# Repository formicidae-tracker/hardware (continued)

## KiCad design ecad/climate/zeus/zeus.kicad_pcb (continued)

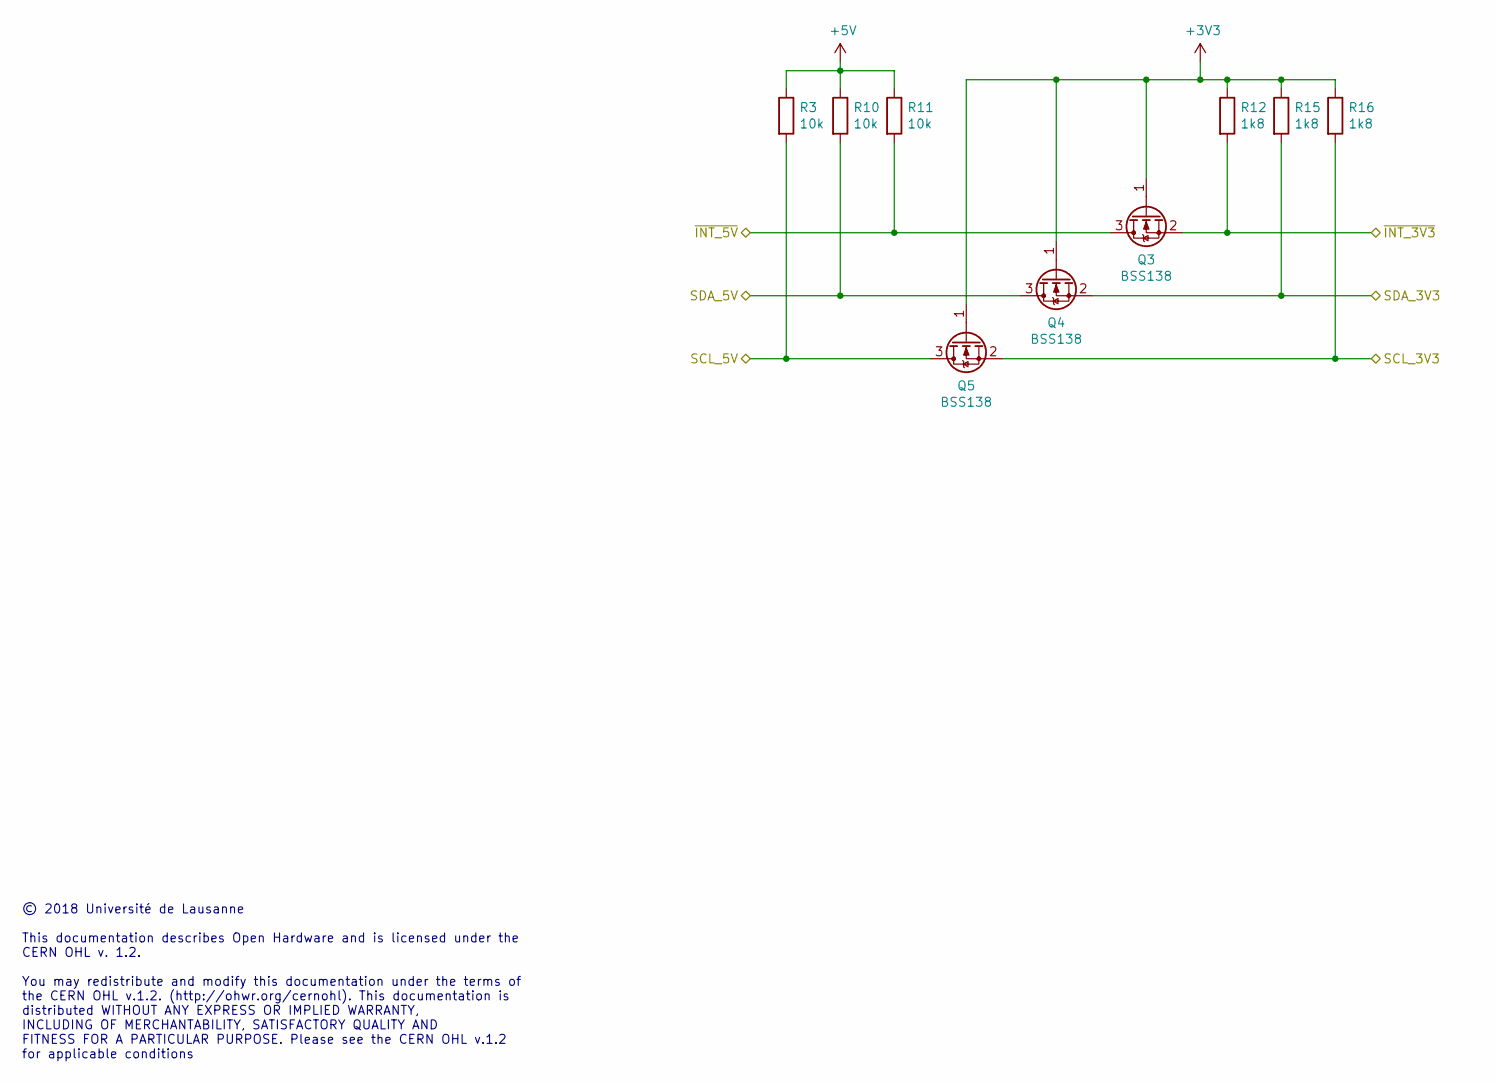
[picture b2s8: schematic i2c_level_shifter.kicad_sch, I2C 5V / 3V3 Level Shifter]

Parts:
Q3, Q4, Q5: BSS138; SOT-23; MPN BSS138
R3, R10, R11: 10k; R_0603_1608Metric; MPN GPR060310K
R12, R15, R16: 1k8; R_0603_1608Metric; MPN GPR06031K8

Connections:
+3V3: Q3.1 (G), Q4.1 (G), Q5.1 (G), R12.1, R15.1, R16.1; also elsewhere on the board
+5V: R3.1, R10.1, R11.1; also elsewhere on the board
/Fan PWM Controller 1/SCL: Q5.2 (S), R16.2; also elsewhere on the board
/Fan PWM Controller 1/SDA: Q4.2 (S), R15.2; also elsewhere on the board
/Fan PWM Controller 1/~ALERT: Q3.2 (S), R12.2; also elsewhere on the board
/I2C Level Shifter/SCL_5V: Q5.3 (D), R3.2; also elsewhere on the board
/I2C Level Shifter/SDA_5V: Q4.3 (D), R10.2; also elsewhere on the board
/I2C Level Shifter/~INT_5V: Q3.3 (D), R11.2; also elsewhere on the board

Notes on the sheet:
© 2018 Université de Lausanne This documentation describes Open Hardware and is licensed under the CERN OHL v. 1.2. You may redistribute and modify this documentation under the terms of the CERN OHL v.1.2. (http://ohwr.org/cernohl). This documentation is distributed WITHOUT ANY EXPRESS OR IMPLIED W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

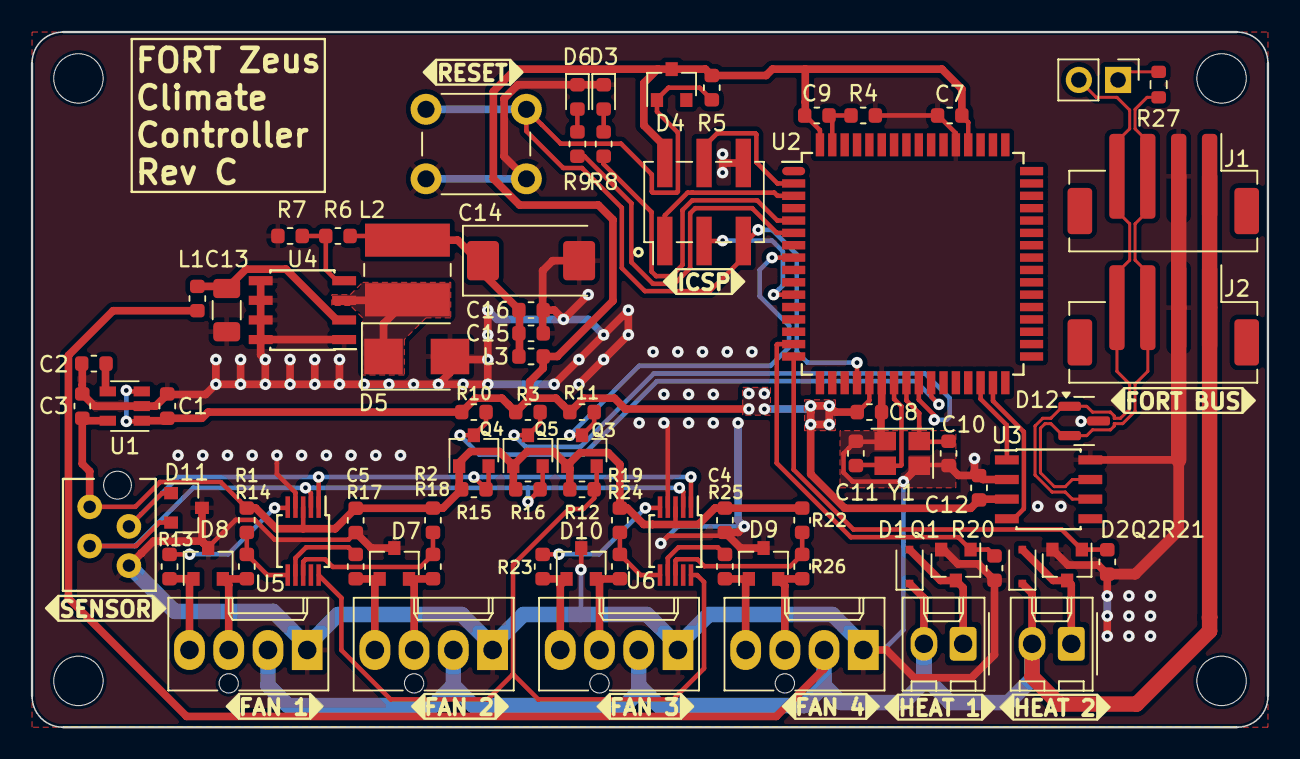
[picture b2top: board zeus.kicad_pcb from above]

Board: 2 copper layers, 80.0 x 45.0 mm, 81 parts (0 on the bottom side), 51 nets.

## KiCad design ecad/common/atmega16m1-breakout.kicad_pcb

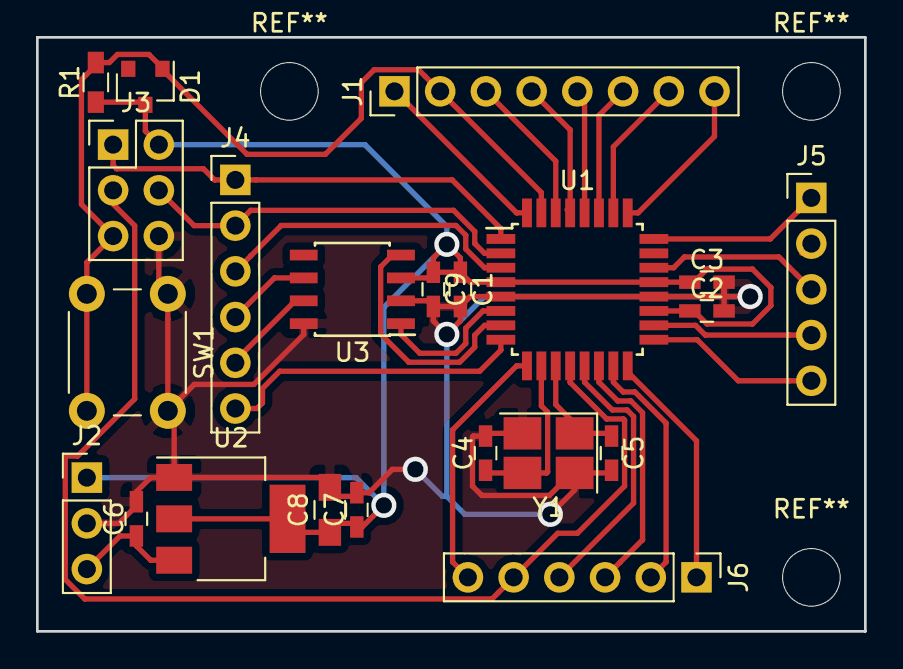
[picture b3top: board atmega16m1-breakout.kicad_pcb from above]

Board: 2 copper layers, 46.0 x 33.0 mm, 22 parts (0 on the bottom side), 32 nets.

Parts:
C1, C2, C3, C6, C7, C9: 100nF; C_0603_HandSoldering
C4, C5: 18pF; C_0603_HandSoldering
C8: 22uF; C_0805_HandSoldering
D1: D_Schottky; D_SOT-23_ANK
J1: Conn_01x08; Pin_Header_Straight_1x08_Pitch2.54mm
J2: Conn_01x03; Pin_Header_Straight_1x03_Pitch2.54mm
J3: Conn_02x03_Odd_Even; Pin_Header_Straight_2x03_Pitch2.54mm
J4, J6: Conn_01x06; Pin_Header_Straight_1x06_Pitch2.54mm
J5: Conn_01x05; Pin_Header_Straight_1x05_Pitch2.54mm
R1: 100K; R_0603_HandSoldering
SW1: SW_Push; SW_PUSH_6mm
U1: ATMEGA16M1-AU; TQFP-32_7x7mm_Pitch0.8mm
U2: NCP1117-5.0_SOT223; SOT-223-3Lead_TabPin2
U3: MCP2561-E/SN; SOIC-8_3.9x4.9mm_Pitch1.27mm
Y1: 16MHz; Crystal_SMD_SeikoEpson_FA238-4pin_3.2x2.5mm_HandSoldering

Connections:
+5V: C1.1, C2.1, C3.1, C7.1, C8.1, C9.1, D1.1, J2.1, J3.2, R1.1, U1.4, U1.19, U1.21, U2.2, U3.3
+BATT: C6.1, J2.3, U2.3
/1: J3.1, J4.1, U1.1
/2: J3.4, J4.2, U1.2
/3: J4.3, U1.3
/8: J4.6, U1.8
/9: J6.6, U1.9
/12: J3.3, J6.5, U1.12
/13: J6.4, U1.13
/14: J6.3, U1.14
/15: J6.2, U1.15
/16: J6.1, U1.16
/17: J5.5, U1.17
/18: J5.4, U1.18
/22: J5.3, U1.22
/23: J5.2, U1.23
/24: J5.1, U1.24
/25: J1.8, U1.25
/26: J1.7, U1.26
/27: J1.6, U1.27
/28: J1.5, U1.28
/29: J1.4, U1.29
/30: J1.3, U1.30
/31: D1.2, J1.2, J3.5, R1.2, SW1.2, U1.31
/32: J1.1, U1.32
/CAN+: J4.5, U3.7
/CAN-: J4.4, U3.6
/RXCAN: U1.7, U3.4
/TXCAN: U1.6, U3.1
/XTAL+: C4.1, U1.10, Y1.3
/XTAL-: C5.1, U1.11, Y1.1
GND: C1.2, C2.2, C3.2, C4.2, C5.2, C6.2, C7.2, C8.2, C9.2, J2.2, J3.6, SW1.1, U1.5, U1.20, U2.1, U3.2, U3.8, Y1.2, Y1.4

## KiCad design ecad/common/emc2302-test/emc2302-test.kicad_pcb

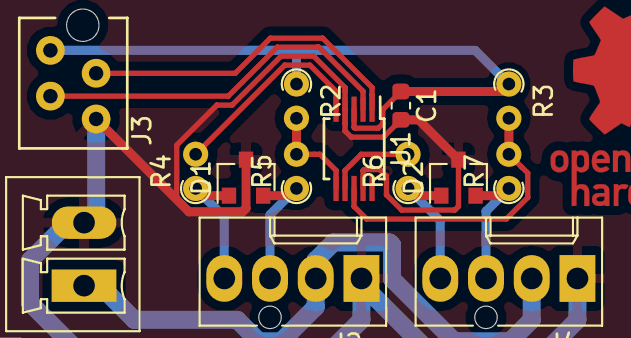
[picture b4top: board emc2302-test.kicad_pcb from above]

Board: 2 copper layers, 14 parts (0 on the bottom side), 13 nets.

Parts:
C1: 100nF; C_0603_1608Metric
D1, D2: CPDT-5V0-HF; SOT-23
J1: Conn_01x02; PhoenixContact_MCV_1,5_2-G-3.5_1x02_P3.50mm_Vertical
J2, J4: Conn_01x04; Molex_KK-47053-04_04x2.54mm_Straight
J3: Conn_01x04; Micro-Match_4_TH
R2, R3: 47k; R_Axial_DIN0204_L3.6mm_D1.6mm_P1.90mm_Vertical
R4, R5, R6, R7: 2k2; R_Axial_DIN0204_L3.6mm_D1.6mm_P1.90mm_Vertical
U1: EMC2302-1-AIZL-TR; MSOP-10_3x3mm_P0.5mm

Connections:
+3V3: C1.1, J3.1, R2.1, R3.1, U1.3
+12V: J1.1, J2.2, J4.2
/Fan Controller/PWM1: D1.1, J2.4, R4.1
/Fan Controller/PWM1_PR: R4.2, U1.5
/Fan Controller/PWM2: D2.1, J4.4, R6.1
/Fan Controller/PWM2_PR: R6.2, U1.7
/Fan Controller/SCL: J3.3, U1.2
/Fan Controller/SDA: J3.2, U1.1
/Fan Controller/TACH1: D1.2, J2.3, R5.1
/Fan Controller/TACH1_PR: R2.2, R5.2, U1.6
/Fan Controller/TACH2: D2.2, J4.3, R7.1
/Fan Controller/TACH2_PR: R3.2, R7.2, U1.8
GND: C1.2, D1.3, D2.3, J1.2, J2.1, J3.4, J4.1, U1.4, U1.9
